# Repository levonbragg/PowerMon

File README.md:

# PowerMon
Licensed using the MIT License

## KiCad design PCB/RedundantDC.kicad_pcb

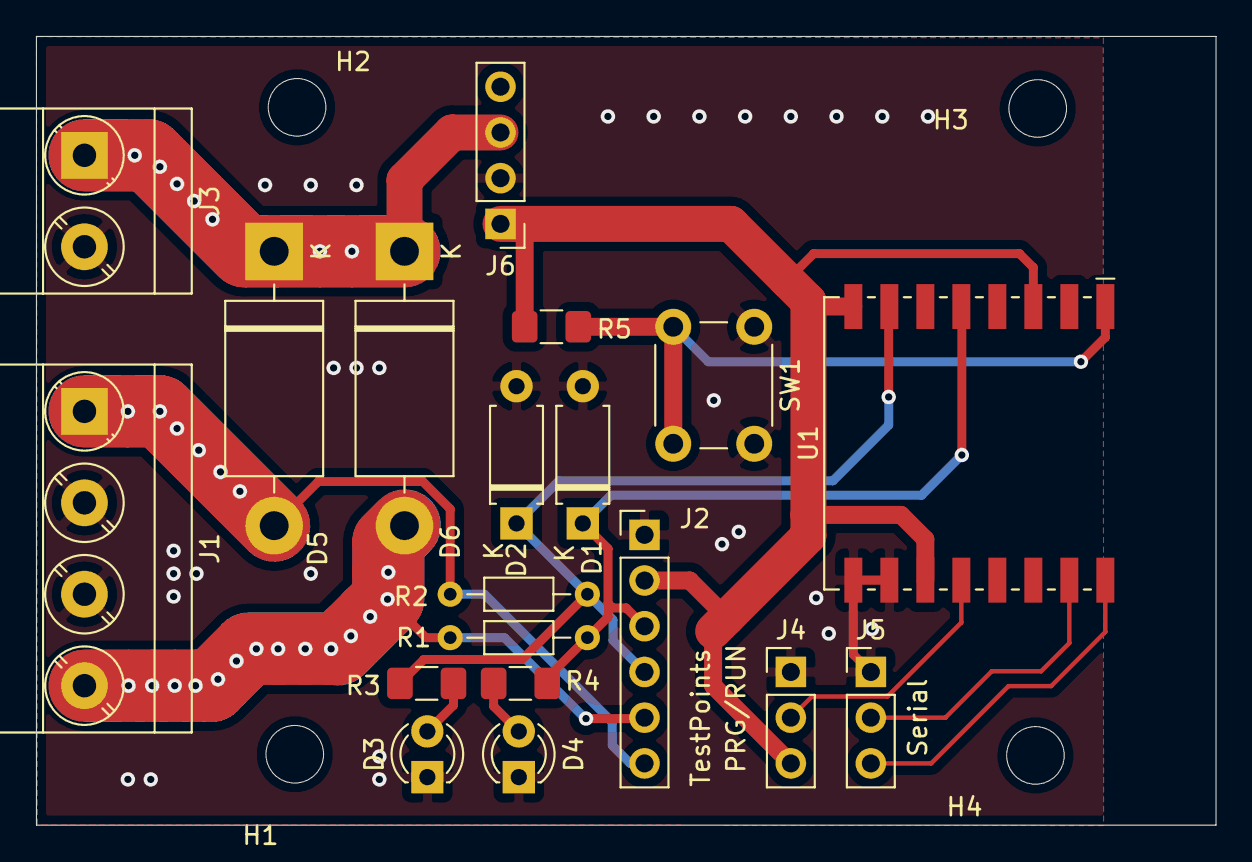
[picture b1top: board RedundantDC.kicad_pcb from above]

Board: 2 copper layers, 65.5 x 43.8 mm, 23 parts (0 on the bottom side), 13 nets.

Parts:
D1, D2: 78-1N4728A; D_A-405_P7.62mm_Horizontal
D3, D4: LED; LED_D3.0mm
D5, D6: 625-SB330-E3/54; D_DO-201AD_P15.24mm_Horizontal
H1, H2, H3, H4: MountingHole; MountingHole_3.2mm_M3
J1: Screw_Terminal_01x04; TerminalBlock_Phoenix_MKDS-3-4-5.08_1x04_P5.08mm_Horizontal
J2: TestPoints; PinHeader_1x06_P2.54mm_Vertical
J3: Screw_Terminal_01x02; TerminalBlock_Phoenix_MKDS-3-2-5.08_1x02_P5.08mm_Horizontal
J4: PRG/RUN; PinHeader_1x03_P2.54mm_Vertical
J5: Serial; PinHeader_1x03_P2.54mm_Vertical
J6: D36V6F3; PinHeader_1x04_P2.54mm_Vertical
R1, R2: 1.4k; R_Axial_DIN0204_L3.6mm_D1.6mm_P7.62mm_Horizontal
R3, R4: 70; R_1206_3216Metric_Pad1.42x1.75mm_HandSolder
R5: 12k; R_1206_3216Metric_Pad1.42x1.75mm_HandSolder
SW1: SW_RST; SW_PUSH_6mm_H4.3mm
U1: ESP-07

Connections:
3v3: J2.2, J4.3, J6.1, R5.1, U1.3, U1.8, U1.11
DC1: D5.2, J1.1, J2.6, R2.2
DC2: D6.2, J1.4, J2.5, R1.2
GND: D1.2, D2.2, D3.1, D4.1, J1.2, J1.3, J2.1, J3.2, J4.1, J5.1, J6.2, SW1.1, U1.9, U1.10
unnamed: D3.2, R3.1
unnamed: D4.2, R4.1
unnamed: J4.2, U1.12
unnamed: J5.2, U1.15
unnamed: J5.3, U1.16
unnamed: R5.2, SW1.2, U1.1
pSense1: D2.1, J2.4, R2.1, R3.2, U1.7
pSense2: D1.1, J2.3, R1.1, R4.2, U1.5
redundantDC: D5.1, D6.1, J3.1, J6.3
